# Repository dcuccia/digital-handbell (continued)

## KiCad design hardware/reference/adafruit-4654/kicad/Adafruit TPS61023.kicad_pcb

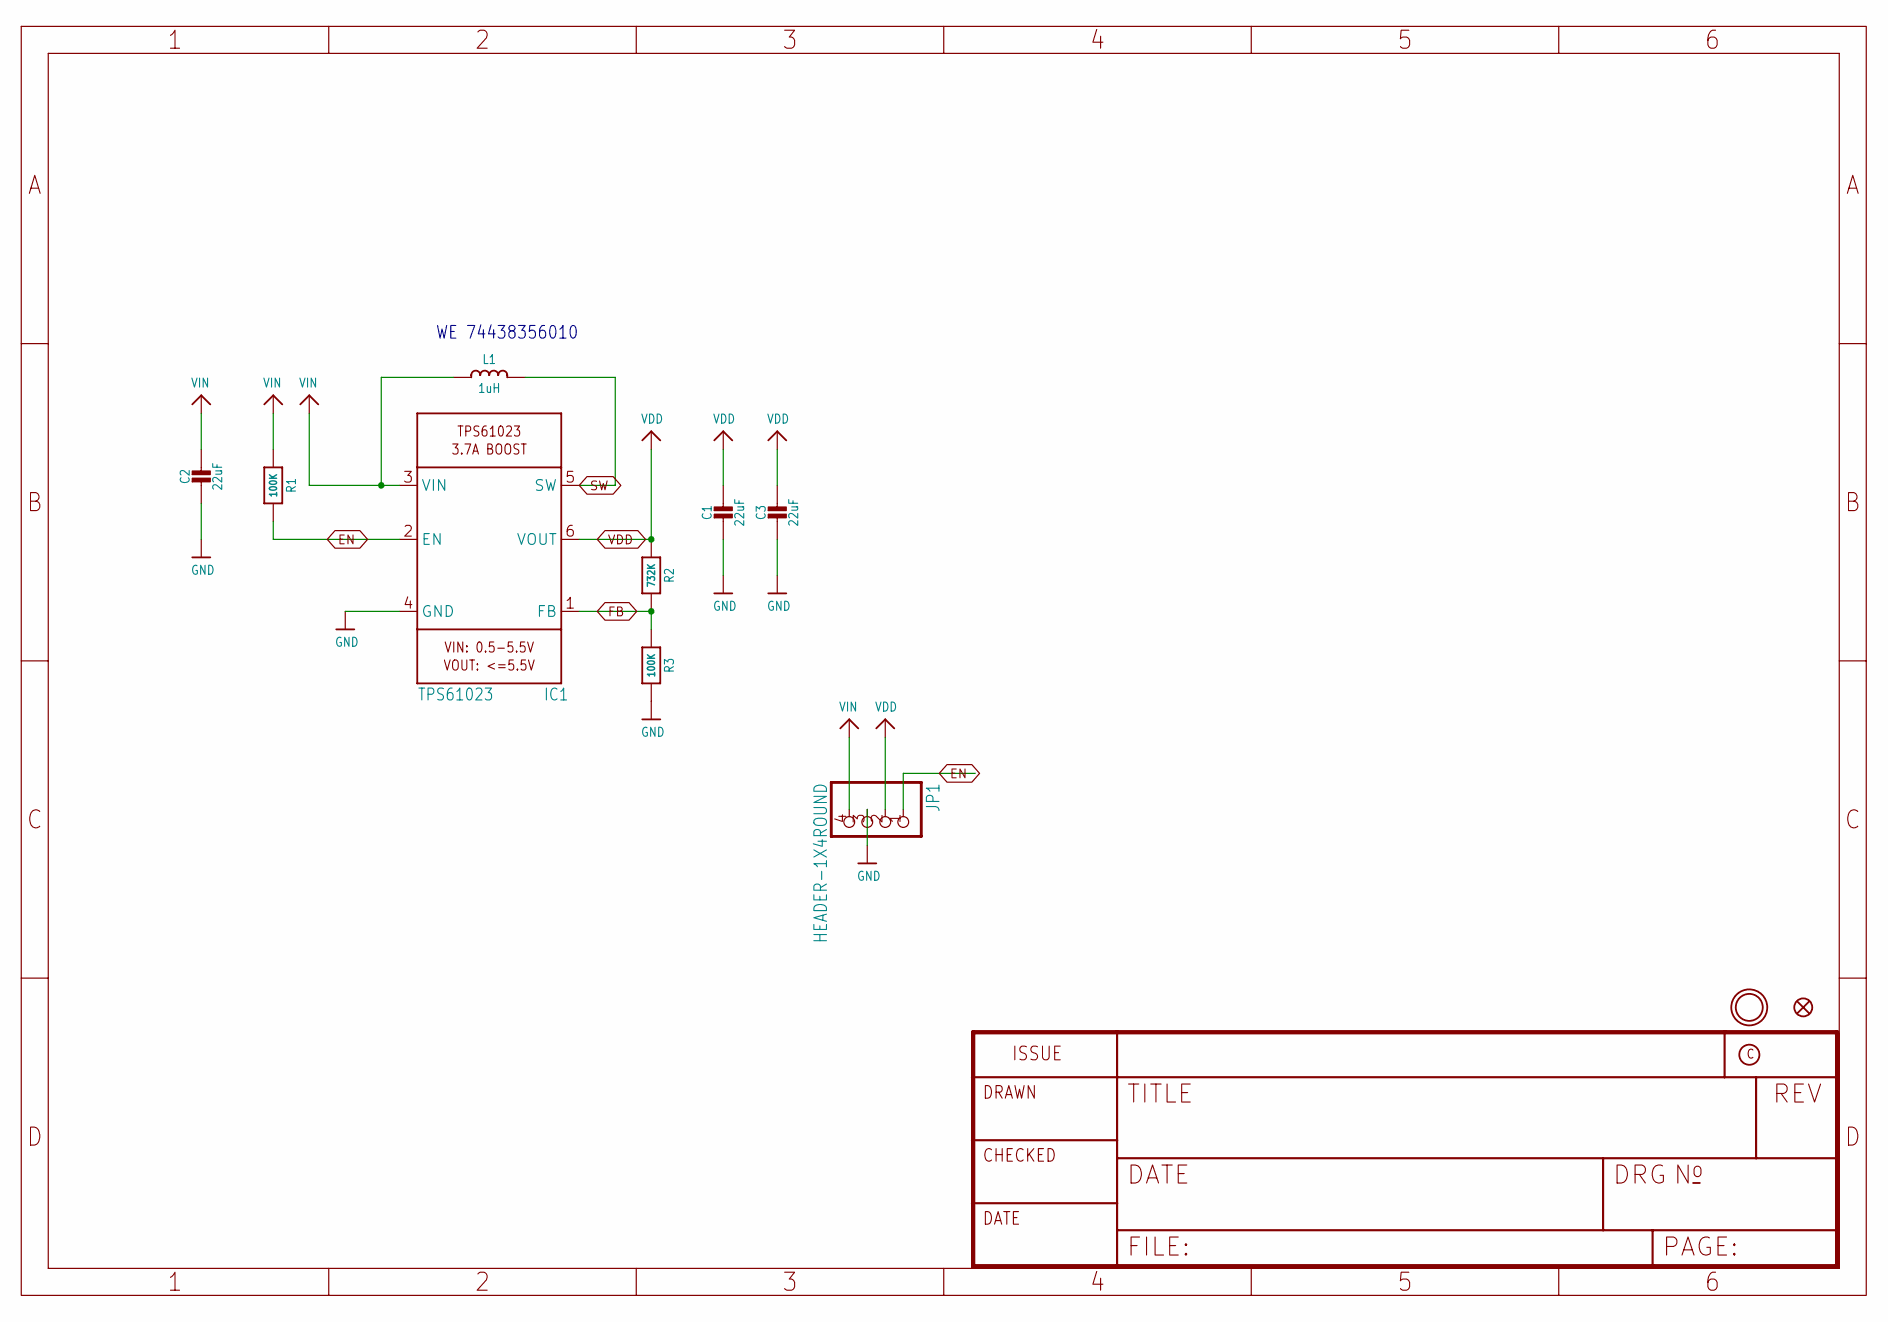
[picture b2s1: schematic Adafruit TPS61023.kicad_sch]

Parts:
C1, C2, C3: 22uF; 0805-NO
FID1: FIDUCIAL_1MM
IC1: TPS61023; SOT563
JP1: HEADER-1X4ROUND; 1X04_ROUND
L1: 1uH; INDUCTOR_5X5MM_TDK_VLC5045
R1, R3: 100K; 0603-NO
R2: 732K; 0603-NO
U$9: MOUNTINGHOLE2.5; MOUNTINGHOLE_2.5_PLATED

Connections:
EN: IC1.2 (EN), JP1.1, R1.2
FB: IC1.1 (FB), R2.2, R3.1
GND: C1.2, C2.2, C3.2, IC1.4 (GND), JP1.3, R3.2
SW: IC1.5 (SW), L1.P$2 (2)
VDD: C1.1, C3.1, IC1.6 (VOUT), JP1.2, R2.1
VIN: C2.1, IC1.3 (VIN), JP1.4, L1.P$1 (1), R1.1

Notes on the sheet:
WE 74438356010

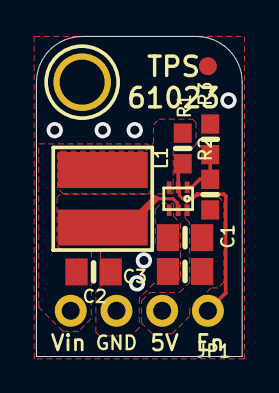
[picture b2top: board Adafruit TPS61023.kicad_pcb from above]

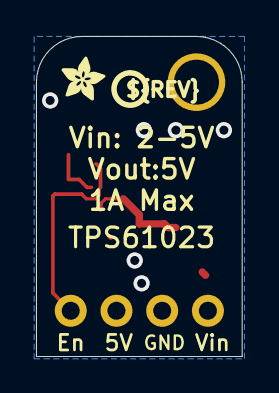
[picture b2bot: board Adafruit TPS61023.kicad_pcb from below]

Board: 2 copper layers, 11.4 x 17.8 mm, 13 parts (2 on the bottom side), 6 nets.

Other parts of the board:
U$10: PCBFEAT-REV-040
U$11: ADAFRUIT_2.5MM

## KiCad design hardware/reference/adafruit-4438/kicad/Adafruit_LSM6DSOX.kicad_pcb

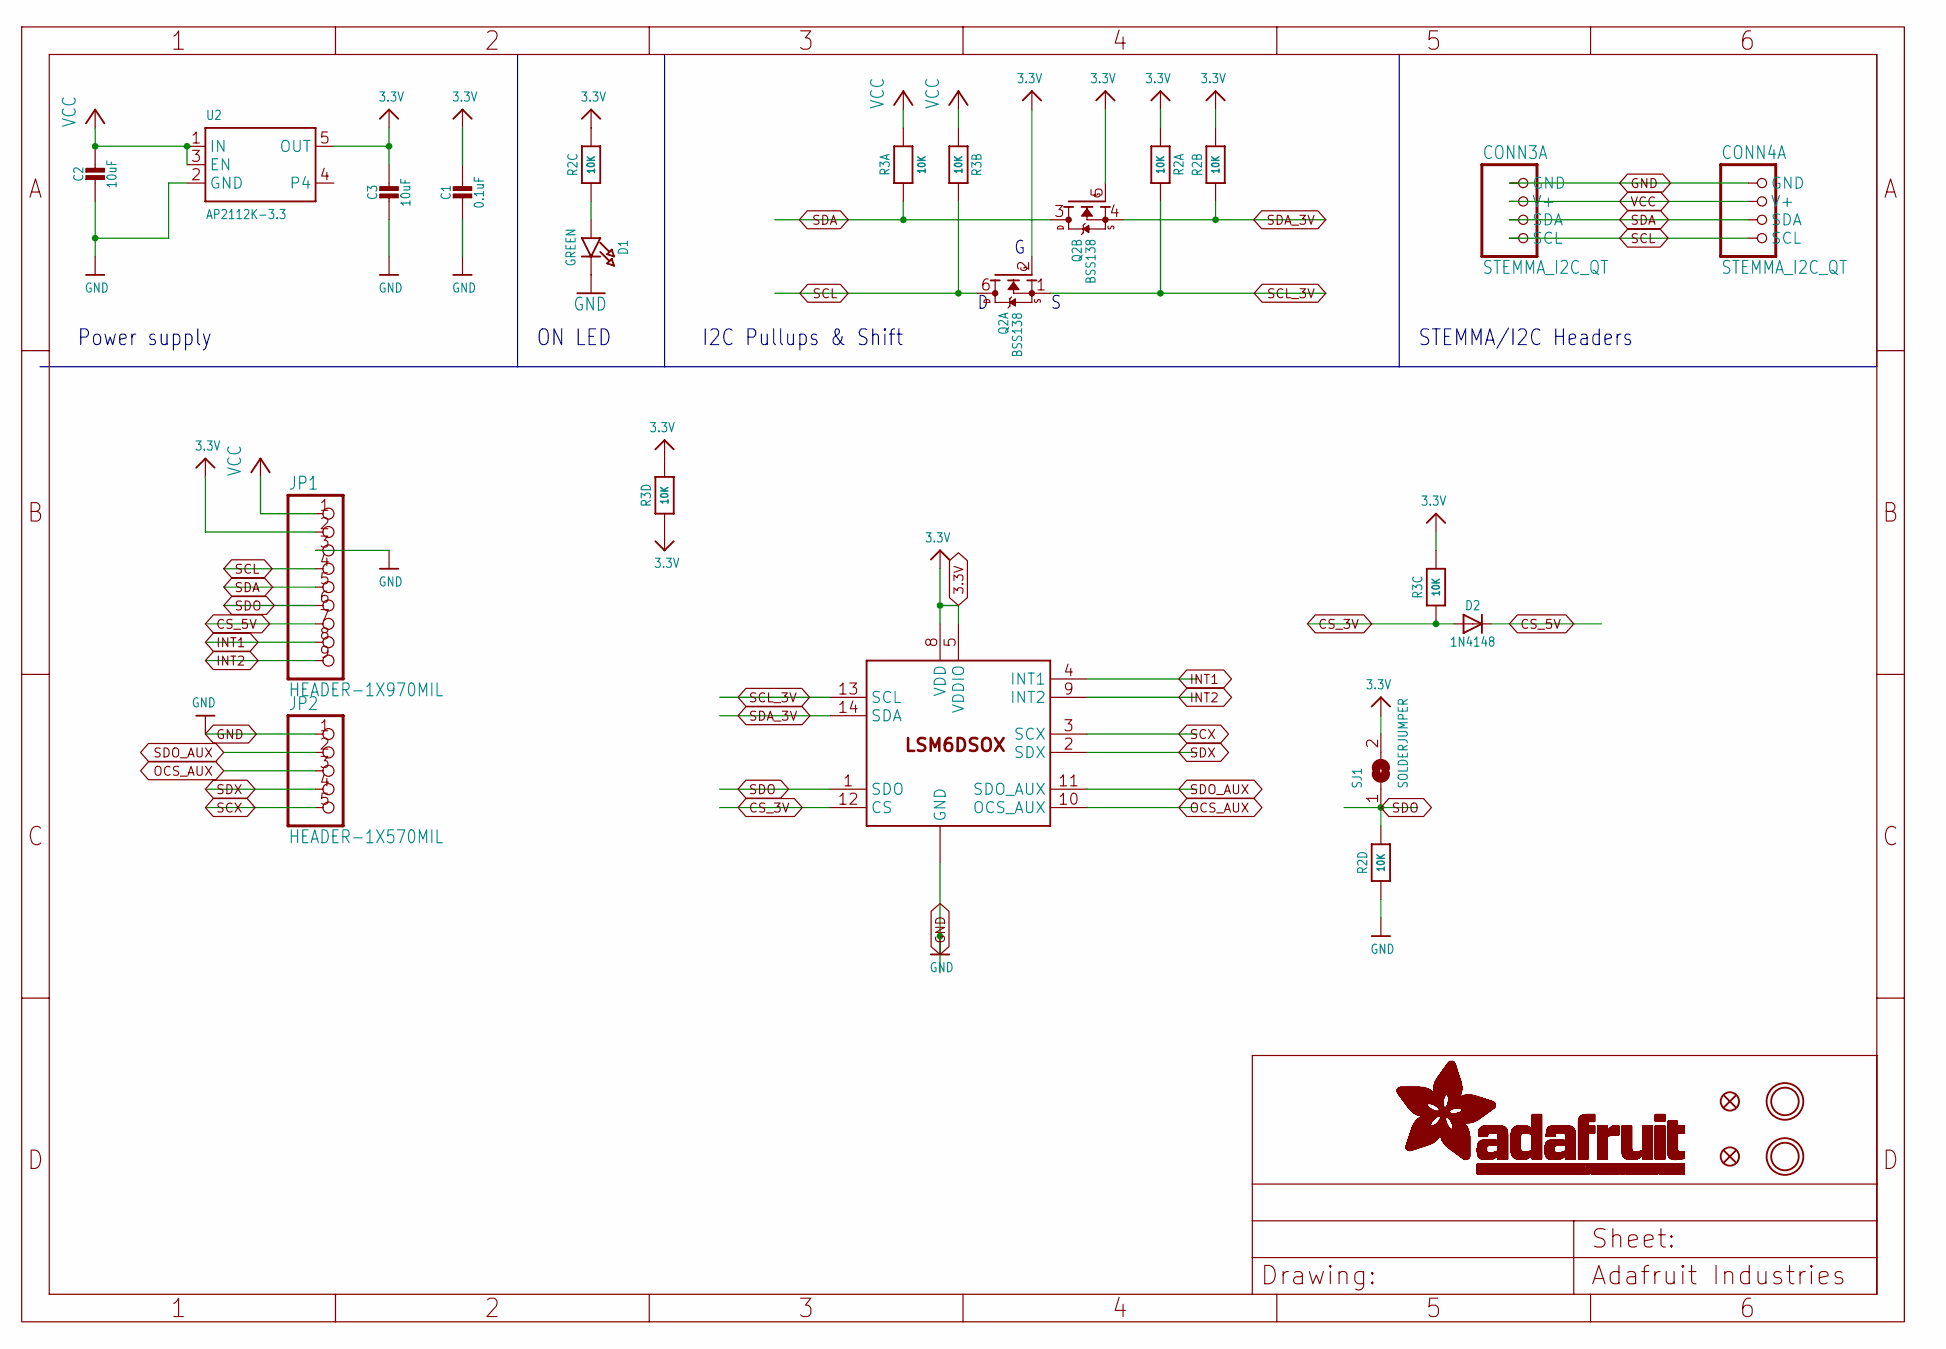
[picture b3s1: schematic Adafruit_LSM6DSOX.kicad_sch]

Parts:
C1: 0.1uF; 0603-NO
C2, C3: 10uF; 0805-NO
CONN3, CONN4: STEMMA_I2C_QT; JST_SH4
D1: GREEN; CHIPLED_0603_NOOUTLINE
D2: 1N4148; SOD-323
FID3, FID4: FIDUCIAL_1MM
JP1: HEADER-1X970MIL; 1X09_ROUND_70
JP2: HEADER-1X570MIL; 1X05_ROUND_70
Q2: BSS138; SOT363
R2, R3: 10K; RESPACK_4X0603
SJ1: SOLDERJUMPER; SOLDERJUMPER_ARROW_NOPASTE
U2: AP2112K-3.3; SOT23-5
U$1, U$17: MOUNTINGHOLE2.5; MOUNTINGHOLE_2.5_PLATED
U$2: LSM6DSOX; LGA-14L

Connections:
3.3V: C1.1, C3.1, JP1.2, Q2.2 (G), Q2.5 (G), R2.1, R2.2 (1), R2.6 (2), R3.3 (1), R3.4 (1), R3.5 (2), SJ1.2, U2.5 (OUT), U$2.5 (VDDIO), U$2.8 (VDD)
CS_3V: D2.A, R3.6 (2), U$2.12 (CS)
CS_5V: D2.C, JP1.7
GND: C1.2, C2.2, C3.2, CONN3.1 (GND), CONN4.1 (GND), D1.C, JP1.3, JP2.1, R2.4 (1), U2.2 (GND), U$2.6 (GND), U$2.7 (GND)
INT1: JP1.8, U$2.4 (INT1)
INT2: JP1.9, U$2.9 (INT2)
unnamed: D1.A, R2.3 (1)
OCS_AUX: JP2.3, U$2.10 (OCS_AUX)
SCL: CONN3.4 (SCL), CONN4.4 (SCL), JP1.4, Q2.6 (D), R3.2 (1)
SCL_3V: Q2.1 (S), R2.8 (2), U$2.13 (SCL)
SCX: JP2.5, U$2.3 (SCX)
SDA: CONN3.3 (SDA), CONN4.3 (SDA), JP1.5, Q2.3 (D), R3.1
SDA_3V: Q2.4 (S), R2.7 (2), U$2.14 (SDA)
SDO: JP1.6, R2.5 (2), SJ1.1, U$2.1 (SDO)
SDO_AUX: JP2.2, U$2.11 (SDO_AUX)
SDX: JP2.4, U$2.2 (SDX)
VCC: C2.1, CONN3.2 (V+), CONN4.2 (V+), JP1.1, R3.7 (2), R3.8 (2), U2.1 (IN), U2.3 (EN)

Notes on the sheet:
ON LED
I2C Pullups & Shift
STEMMA/I2C Headers
Power supply

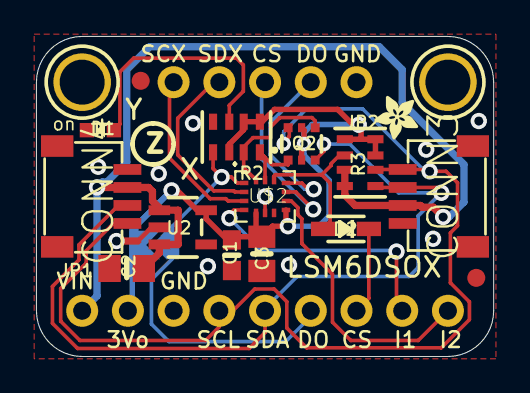
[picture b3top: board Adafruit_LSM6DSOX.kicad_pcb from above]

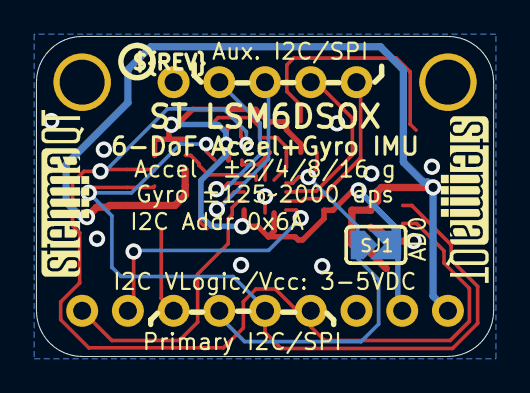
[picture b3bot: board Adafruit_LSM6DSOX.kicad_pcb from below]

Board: 2 copper layers, 25.4 x 17.8 mm, 23 parts (4 on the bottom side), 17 nets.

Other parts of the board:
U$9: ADAFRUIT_2.5MM
U$25: PCBFEAT-REV-040
U$30, U$31: STEMMAQT

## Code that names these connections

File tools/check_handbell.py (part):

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        for pin, name in pin_map.items():
            require(pin_nets.get((ref, pin)) == name, f"{ref}.{pin} must connect to {name}.")
    for pin in AMP_MOVED:
        require(pin_nets.get(pin) == "VAMP", f"{pin}: amplifier rail not moved to boost output.")
    for ref, value in NEW_VALUES.items():
        require(draft_components[ref].findtext("value") == value, f"{ref}: expected {value}.")
    require(pin_nets.get(("IC1", "30")) == "BUTTON", "User button must use GPIO19.")
    require(pin_nets.get(("IC1", "31")) == "AMP_MUTE", "Mute must use GPIO20.")
    _, native_schematic = load(paths["handbell"])
    dnp = {s.properties()["Reference"] for s in native_schematic.children("symbol") if s.value("dnp") == "yes"}
    require(dnp == {"C29"}, "Only the unresolved feed-forward option C29 should be DNP.")
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
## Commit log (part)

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2023-03-26 2023-03-25 Episode 0 notes
2023-03-26 Change notes to markdown
2023-03-26 Added ESP32 QT Py option (with WiFI)
2023-03-26 Cleared design notes
2023-03-26 Initial parts to consider
2023-03-26 Add system diagram
